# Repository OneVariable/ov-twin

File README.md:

# OneVariable Twin Trainer Hardware

Hardware for the OV Twin Trainer Board.

Designed for [RustNL 2024 Workshops](https://2024.rustnl.org/workshops/)

## Schematic

You can view the PDF schematic [here](./assets/ov-twin.pdf).

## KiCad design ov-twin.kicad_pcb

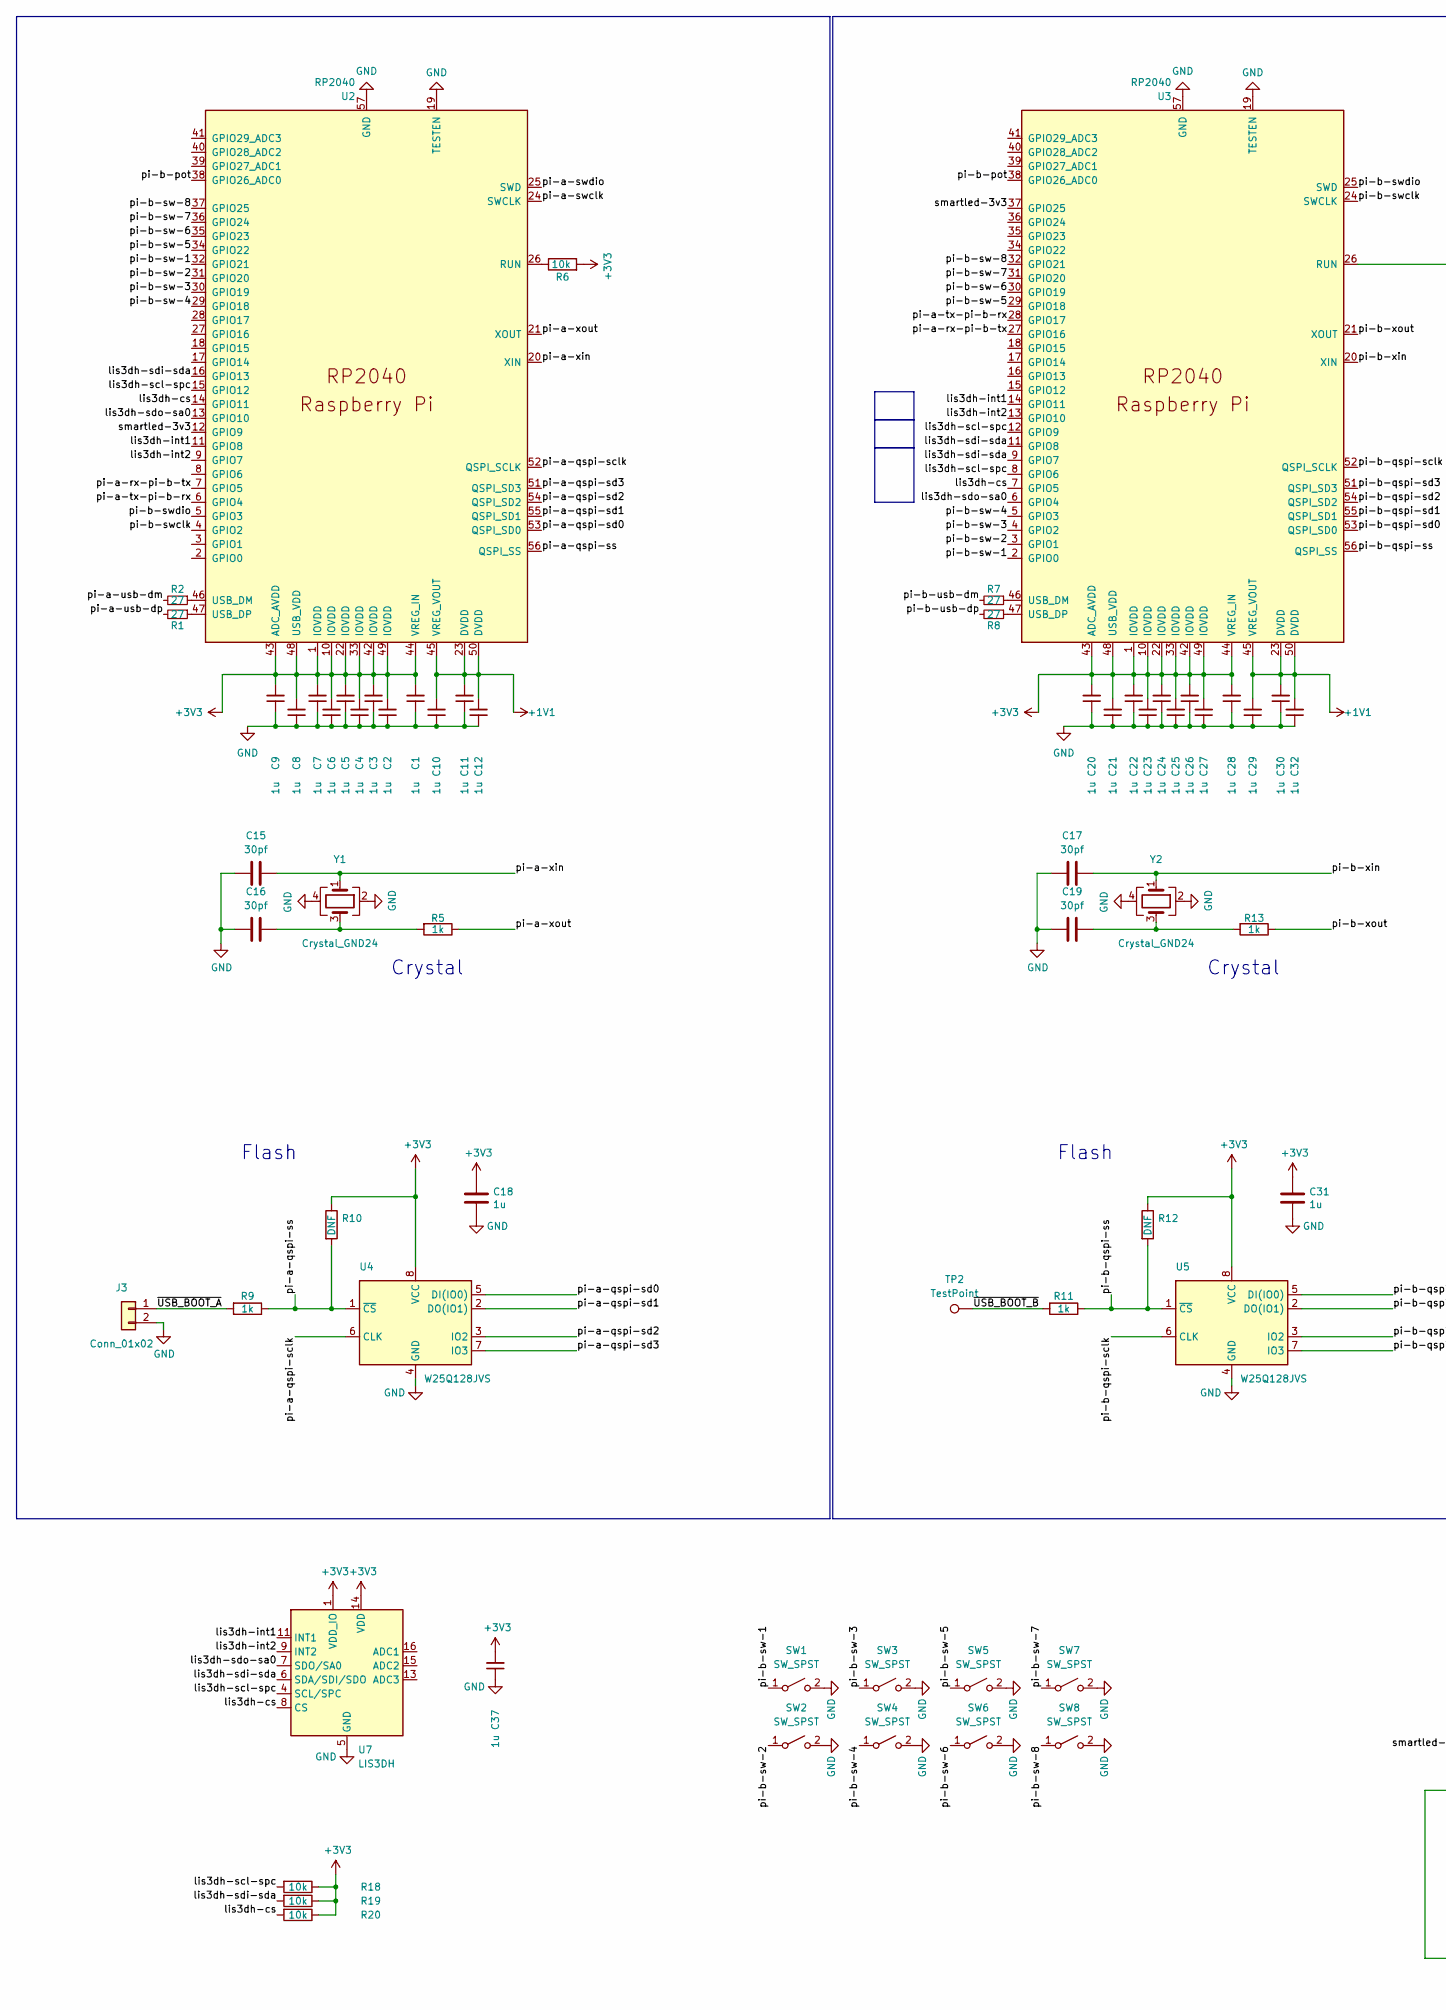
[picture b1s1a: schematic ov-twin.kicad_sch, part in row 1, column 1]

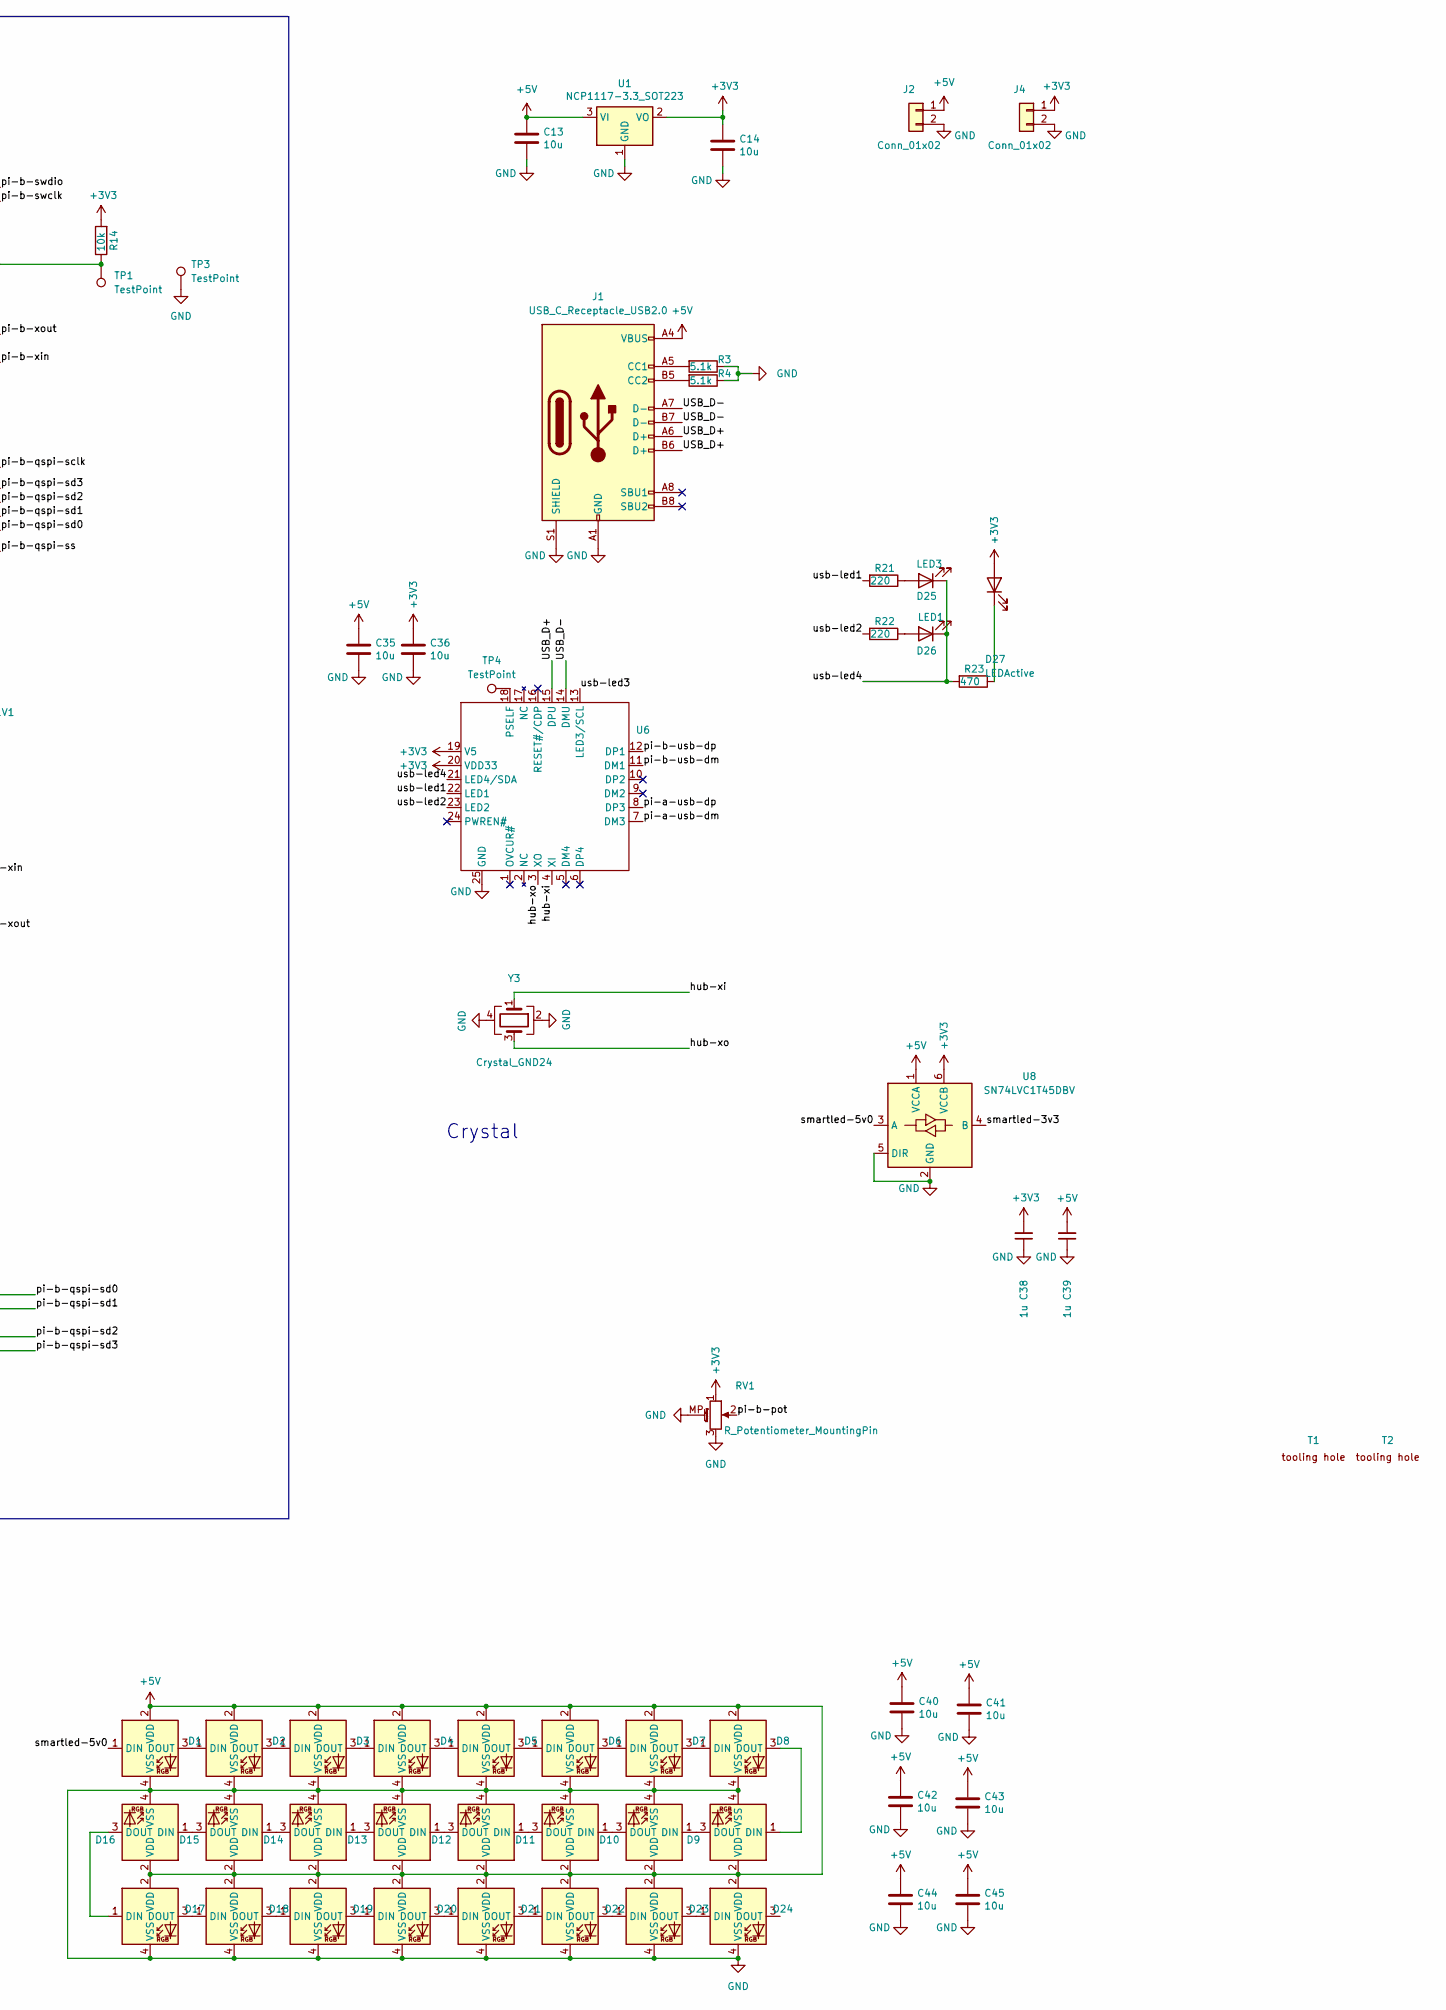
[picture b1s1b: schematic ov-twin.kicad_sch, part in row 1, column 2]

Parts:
C1, C2, C3, C4, C5, C6, C7, C8, C9, C10, C11, C12, C20, C21, C22, C23, C24, C25, C26, C27, C28, C29, C30, C32, C37, C38, C39: 1u; C_0402_1005Metric
C13, C14, C35, C36, C40, C41, C42, C43, C44, C45: 10u; C_0805_2012Metric
C15, C16, C17, C19: 30pf; C_0603_1608Metric
C18, C31: 1u; C_0805_2012Metric
D1, D2, D3, D4, D5, D6, D7, D8, D9, D10, D11, D12, D13, D14, D15, D16, D17, D18, D19, D20, D21, D22, D23, D24: LED_WS2812B-2020_PLCC4_2.0x2.0mm
D25: LED3; LED_0603_1608Metric
D26: LED1; LED_0603_1608Metric
D27: LEDActive; LED_0603_1608Metric
J1: USB_C_Receptacle_USB2.0; USB_C_Receptacle_G-Switch_GT-USB-7010ASV
J2, J3, J4: Conn_01x02; PinHeader_1x02_P2.54mm_Vertical
R1, R2, R7, R8: 27; R_0402_1005Metric
R3, R4: 5.1k; R_0402_1005Metric
R5, R9, R11, R13: 1k; R_0402_1005Metric
R6, R14, R18, R19, R20: 10k; R_0402_1005Metric
R10, R12: DNF; R_0402_1005Metric
R21, R22: 220; R_0402_1005Metric
R23: 470; R_0402_1005Metric
RV1: R_Potentiometer_MountingPin; Potentiometer_Alps_RK09K_Single_Vertical
SW1, SW2, SW3, SW4, SW5, SW6, SW7, SW8: SW_SPST; k2-1817UQ
T1, T2: tooling-hole
TP1, TP2, TP3, TP4: TestPoint; TestPoint_Pad_D1.5mm
U1: NCP1117-3.3_SOT223; SOT-223-3_TabPin2
U2, U3: RP2040; RP2040-QFN-56
U4, U5: W25Q128JVS; SOIC-8_5.23x5.23mm_P1.27mm
U6: QFN-24-1EP_4x4mm_P0.5mm_EP2.7x2.7mm_ThermalVias
U7: LIS3DH; LGA-16_3x3mm_P0.5mm_LayoutBorder3x5y
U8: SN74LVC1T45DBV; SOT-23-6
Y1, Y2, Y3: Crystal_GND24; Crystal_SMD_3225-4Pin_3.2x2.5mm

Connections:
+1V1: C10.2, C11.2, C12.2, C29.2, C30.2, C32.2, U2.23 (DVDD), U2.45 (VREG_VOUT), U2.50 (DVDD), U3.23 (DVDD), U3.45 (VREG_VOUT), U3.50 (DVDD)
+3V3: C1.2, C2.2, C3.2, C4.2, C5.2, C6.2, C7.2, C8.2, C9.2, C14.1, C18.1, C20.2, C21.2, C22.2, C23.2, C24.2, C25.2, C26.2, C27.2, C28.2, C31.1, C36.1, C37.2, C38.2, D27.2 (A), J4.1, R6.2, R10.1, R12.1, R14.2, R18.1, R19.1, R20.1, RV1.1, U1.2 (VO), U2.1 (IOVDD), U2.10 (IOVDD), U2.22 (IOVDD), U2.33 (IOVDD), U2.42 (IOVDD), U2.43 (ADC_AVDD), U2.44 (VREG_IN), U2.48 (USB_VDD), U2.49 (IOVDD), U3.1 (IOVDD), U3.10 (IOVDD), U3.22 (IOVDD), U3.33 (IOVDD), U3.42 (IOVDD), U3.43 (ADC_AVDD), U3.44 (VREG_IN), U3.48 (USB_VDD), U3.49 (IOVDD), U4.8 (VCC), U5.8 (VCC), U6.19 (V5), U6.20 (VDD33), U7.1 (VDD_IO), U7.14 (VDD), U8.6 (VCCB)
+5V: C13.1, C35.1, C39.2, C40.1, C41.1, C42.1, C43.1, C44.1, C45.1, D1.2 (VDD), D2.2 (VDD), D3.2 (VDD), D4.2 (VDD), D5.2 (VDD), D6.2 (VDD), D7.2 (VDD), D8.2 (VDD), D9.2 (VDD), D10.2 (VDD), D11.2 (VDD), D12.2 (VDD), D13.2 (VDD), D14.2 (VDD), D15.2 (VDD), D16.2 (VDD), D17.2 (VDD), D18.2 (VDD), D19.2 (VDD), D20.2 (VDD), D21.2 (VDD), D22.2 (VDD), D23.2 (VDD), D24.2 (VDD), J1.A4 (VBUS), J1.A9 (VBUS), J1.B4 (VBUS), J1.B9 (VBUS), J2.1, U1.3 (VI), U8.1 (VCCA)
/USB_D+: J1.A6 (D+), J1.B6 (D+), U6.15 (DPU)
/USB_D-: J1.A7 (D-), J1.B7 (D-), U6.14 (DMU)
/hub-xi: U6.4 (XI), Y3.1
/hub-xo: U6.3 (XO), Y3.3
/lis3dh-cs: R20.2, U2.14 (GPIO11), U3.7 (GPIO5), U7.8 (CS)
/lis3dh-int1: U2.11 (GPIO8), U3.14 (GPIO11), U7.11 (INT1)
/lis3dh-int2: U2.9 (GPIO7), U3.13 (GPIO10), U7.9 (INT2)
/lis3dh-scl-spc: R18.2, U2.15 (GPIO12), U3.8 (GPIO6), U3.12 (GPIO9), U7.4 (SCL/SPC)
/lis3dh-sdi-sda: R19.2, U2.16 (GPIO13), U3.9 (GPIO7), U3.11 (GPIO8), U7.6 (SDA/SDI/SDO)
/lis3dh-sdo-sa0: U2.13 (GPIO10), U3.6 (GPIO4), U7.7 (SDO/SA0)
/pi-a-qspi-sclk: U2.52 (QSPI_SCLK), U4.6 (CLK)
/pi-a-qspi-sd0: U2.53 (QSPI_SD0), U4.5 (DI(IO0))
/pi-a-qspi-sd1: U2.55 (QSPI_SD1), U4.2 (DO(IO1))
/pi-a-qspi-sd2: U2.54 (QSPI_SD2), U4.3 (IO2)
/pi-a-qspi-sd3: U2.51 (QSPI_SD3), U4.7 (IO3)
/pi-a-qspi-ss: R9.1, R10.2, U2.56 (QSPI_SS), U4.1 (~CS)
/pi-a-rx-pi-b-tx: U2.7 (GPIO5), U3.27 (GPIO16)
/pi-a-swclk: U2.24 (SWCLK)
/pi-a-swdio: U2.25 (SWD)
/pi-a-tx-pi-b-rx: U2.6 (GPIO4), U3.28 (GPIO17)
/pi-a-usb-dm: R2.2, U6.7 (DM3)
/pi-a-usb-dp: R1.2, U6.8 (DP3)
/pi-a-xin: C15.2, U2.20 (XIN), Y1.1
/pi-a-xout: R5.1, U2.21 (XOUT)
/pi-b-pot: RV1.2, U2.38 (GPIO26_ADC0), U3.38 (GPIO26_ADC0)
/pi-b-qspi-sclk: U3.52 (QSPI_SCLK), U5.6 (CLK)
/pi-b-qspi-sd0: U3.53 (QSPI_SD0), U5.5 (DI(IO0))
/pi-b-qspi-sd1: U3.55 (QSPI_SD1), U5.2 (DO(IO1))
/pi-b-qspi-sd2: U3.54 (QSPI_SD2), U5.3 (IO2)
/pi-b-qspi-sd3: U3.51 (QSPI_SD3), U5.7 (IO3)
/pi-b-qspi-ss: R11.1, R12.2, U3.56 (QSPI_SS), U5.1 (~CS)
/pi-b-sw-1: SW1.1 (A), U2.32 (GPIO21), U3.2 (GPIO0)
/pi-b-sw-2: SW2.1 (A), U2.31 (GPIO20), U3.3 (GPIO1)
/pi-b-sw-3: SW3.1 (A), U2.30 (GPIO19), U3.4 (GPIO2)
/pi-b-sw-4: SW4.1 (A), U2.29 (GPIO18), U3.5 (GPIO3)
/pi-b-sw-5: SW5.1 (A), U2.34 (GPIO22), U3.29 (GPIO18)
/pi-b-sw-6: SW6.1 (A), U2.35 (GPIO23), U3.30 (GPIO19)
/pi-b-sw-7: SW7.1 (A), U2.36 (GPIO24), U3.31 (GPIO20)
/pi-b-sw-8: SW8.1 (A), U2.37 (GPIO25), U3.32 (GPIO21)
/pi-b-swclk: U2.4 (GPIO2), U3.24 (SWCLK)
/pi-b-swdio: U2.5 (GPIO3), U3.25 (SWD)
/pi-b-usb-dm: R7.2, U6.11 (DM1)
/pi-b-usb-dp: R8.2, U6.12 (DP1)
/pi-b-xin: C17.2, U3.20 (XIN), Y2.1
/pi-b-xout: R13.1, U3.21 (XOUT)
/smartled-3v3: U2.12 (GPIO9), U3.37 (GPIO25), U8.4 (B)
/smartled-5v0: D1.1 (DIN), U8.3 (A)
/usb-led1: R21.2, U6.22 (LED1)
/usb-led2: R22.2, U6.23 (LED2)
/usb-led3: U6.13 (LED3/SCL)
/usb-led4: D25.1 (K), D26.1 (K), R23.2, U6.21 (LED4/SDA)
/~USB_BOOT_A: J3.1, R9.2
/~USB_BOOT_B: R11.2, TP2.1
GND: C1.1, C2.1, C3.1, C4.1, C5.1, C6.1, C7.1, C8.1, C9.1, C10.1, C11.1, C12.1, C13.2, C14.2, C15.1, C16.1, C17.1, C18.2, C19.1, C20.1, C21.1, C22.1, C23.1, C24.1, C25.1, C26.1, C27.1, C28.1, C29.1, C30.1, C31.2, C32.1, C35.2, C36.2, C37.1, C38.1, C39.1, C40.2, C41.2, C42.2, C43.2, C44.2, C45.2, D1.4 (VSS), D2.4 (VSS), D3.4 (VSS), D4.4 (VSS), D5.4 (VSS), D6.4 (VSS), D7.4 (VSS), D8.4 (VSS), D9.4 (VSS), D10.4 (VSS), D11.4 (VSS), D12.4 (VSS), D13.4 (VSS), D14.4 (VSS), D15.4 (VSS), D16.4 (VSS), D17.4 (VSS), D18.4 (VSS), D19.4 (VSS), D20.4 (VSS), D21.4 (VSS), D22.4 (VSS), D23.4 (VSS), D24.4 (VSS), J1.A1 (GND), J1.A12 (GND), J1.B1 (GND), J1.B12 (GND), J1.S1 (SHIELD), J2.2, J3.2, J4.2, R3.1, R4.1, RV1.3, RV1.MP (MountPin), SW1.2 (B), SW2.2 (B), SW3.2 (B), SW4.2 (B), SW5.2 (B), SW6.2 (B), SW7.2 (B), SW8.2 (B), TP3.1, U1.1 (GND), U2.19 (TESTEN), U2.57 (GND), U3.19 (TESTEN), U3.57 (GND), U4.4 (GND), U5.4 (GND), U6.25 (GND), U7.5 (GND), U7.10 (GND), U7.12 (GND), U8.2 (GND), U8.5 (DIR), Y1.2, Y1.4, Y2.2, Y2.4, Y3.2, Y3.4
unnamed: C16.2, R5.2, Y1.3
unnamed: C19.2, R13.2, Y2.3
unnamed: D1.3 (DOUT), D2.1 (DIN)
unnamed: D2.3 (DOUT), D3.1 (DIN)
unnamed: D3.3 (DOUT), D4.1 (DIN)
unnamed: D4.3 (DOUT), D5.1 (DIN)
unnamed: D5.3 (DOUT), D6.1 (DIN)
unnamed: D6.3 (DOUT), D7.1 (DIN)
unnamed: D7.3 (DOUT), D8.1 (DIN)
unnamed: D8.3 (DOUT), D9.1 (DIN)
unnamed: D9.3 (DOUT), D10.1 (DIN)
unnamed: D10.3 (DOUT), D11.1 (DIN)
unnamed: D11.3 (DOUT), D12.1 (DIN)
unnamed: D12.3 (DOUT), D13.1 (DIN)
unnamed: D13.3 (DOUT), D14.1 (DIN)
unnamed: D14.3 (DOUT), D15.1 (DIN)
unnamed: D15.3 (DOUT), D16.1 (DIN)
unnamed: D16.3 (DOUT), D17.1 (DIN)
unnamed: D17.3 (DOUT), D18.1 (DIN)
unnamed: D18.3 (DOUT), D19.1 (DIN)
unnamed: D19.3 (DOUT), D20.1 (DIN)
unnamed: D20.3 (DOUT), D21.1 (DIN)
unnamed: D21.3 (DOUT), D22.1 (DIN)
unnamed: D22.3 (DOUT), D23.1 (DIN)
unnamed: D23.3 (DOUT), D24.1 (DIN)
unnamed: D25.2 (A), R21.1
unnamed: D26.2 (A), R22.1
unnamed: D27.1 (K), R23.1
unnamed: J1.A5 (CC1), R3.2
unnamed: J1.B5 (CC2), R4.2
unnamed: R6.1, U2.26 (RUN)
unnamed: R2.1, U2.46 (USB_DM)
unnamed: R1.1, U2.47 (USB_DP)
unnamed: R14.1, TP1.1, U3.26 (RUN)
unnamed: R7.1, U3.46 (USB_DM)
unnamed: R8.1, U3.47 (USB_DP)
unnamed: TP4.1, U6.18 (PSELF)

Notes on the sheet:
Crystal
Flash

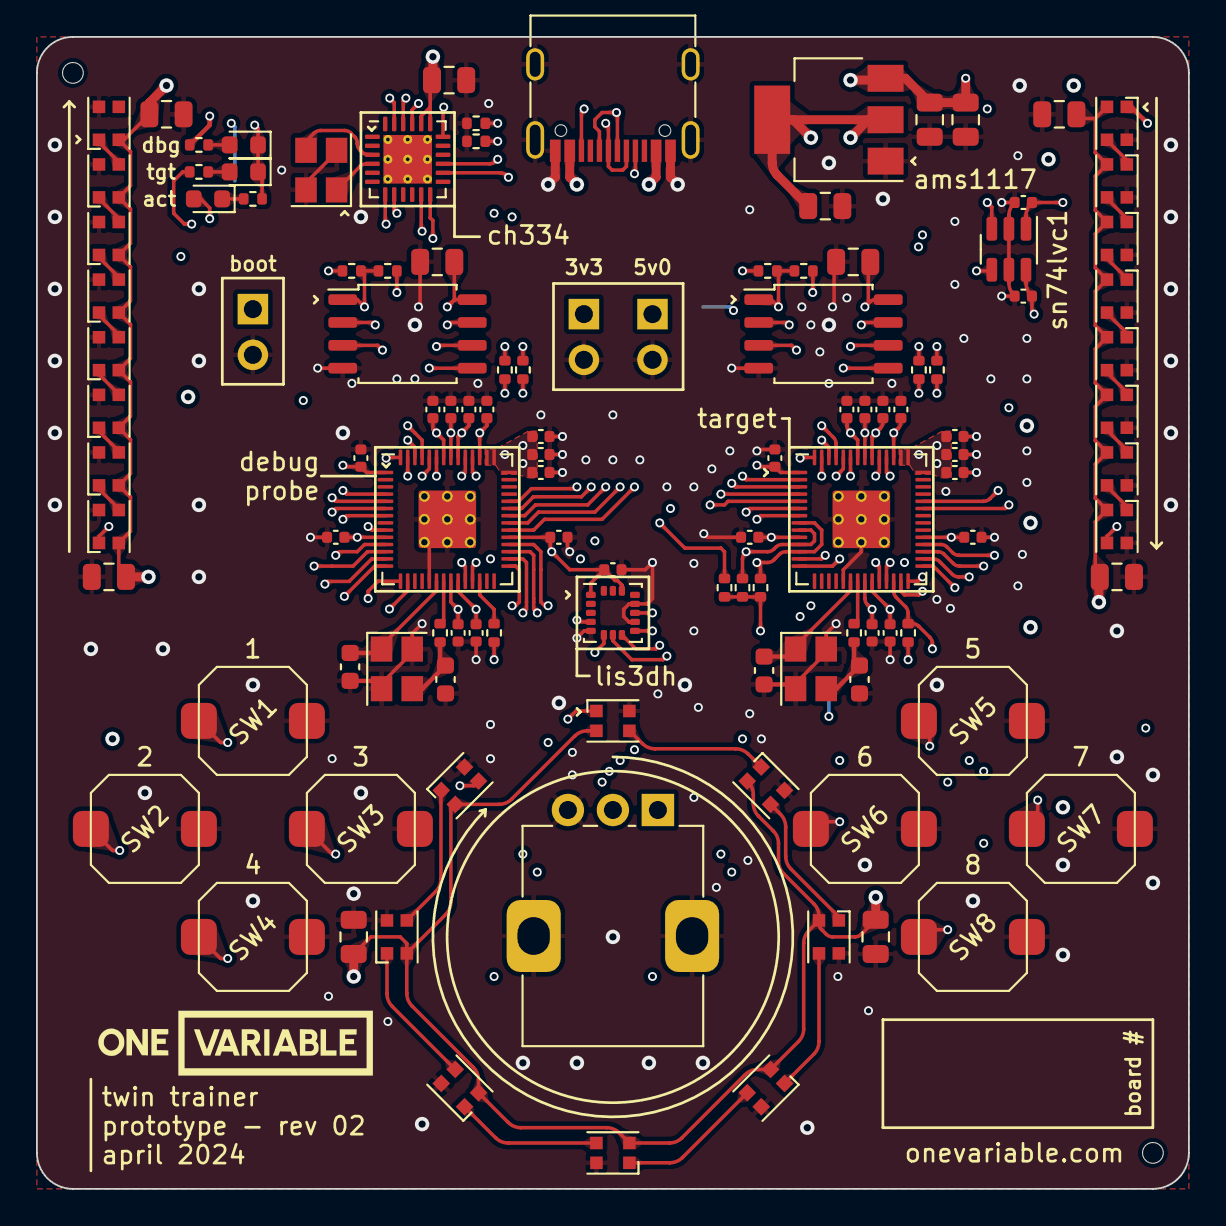
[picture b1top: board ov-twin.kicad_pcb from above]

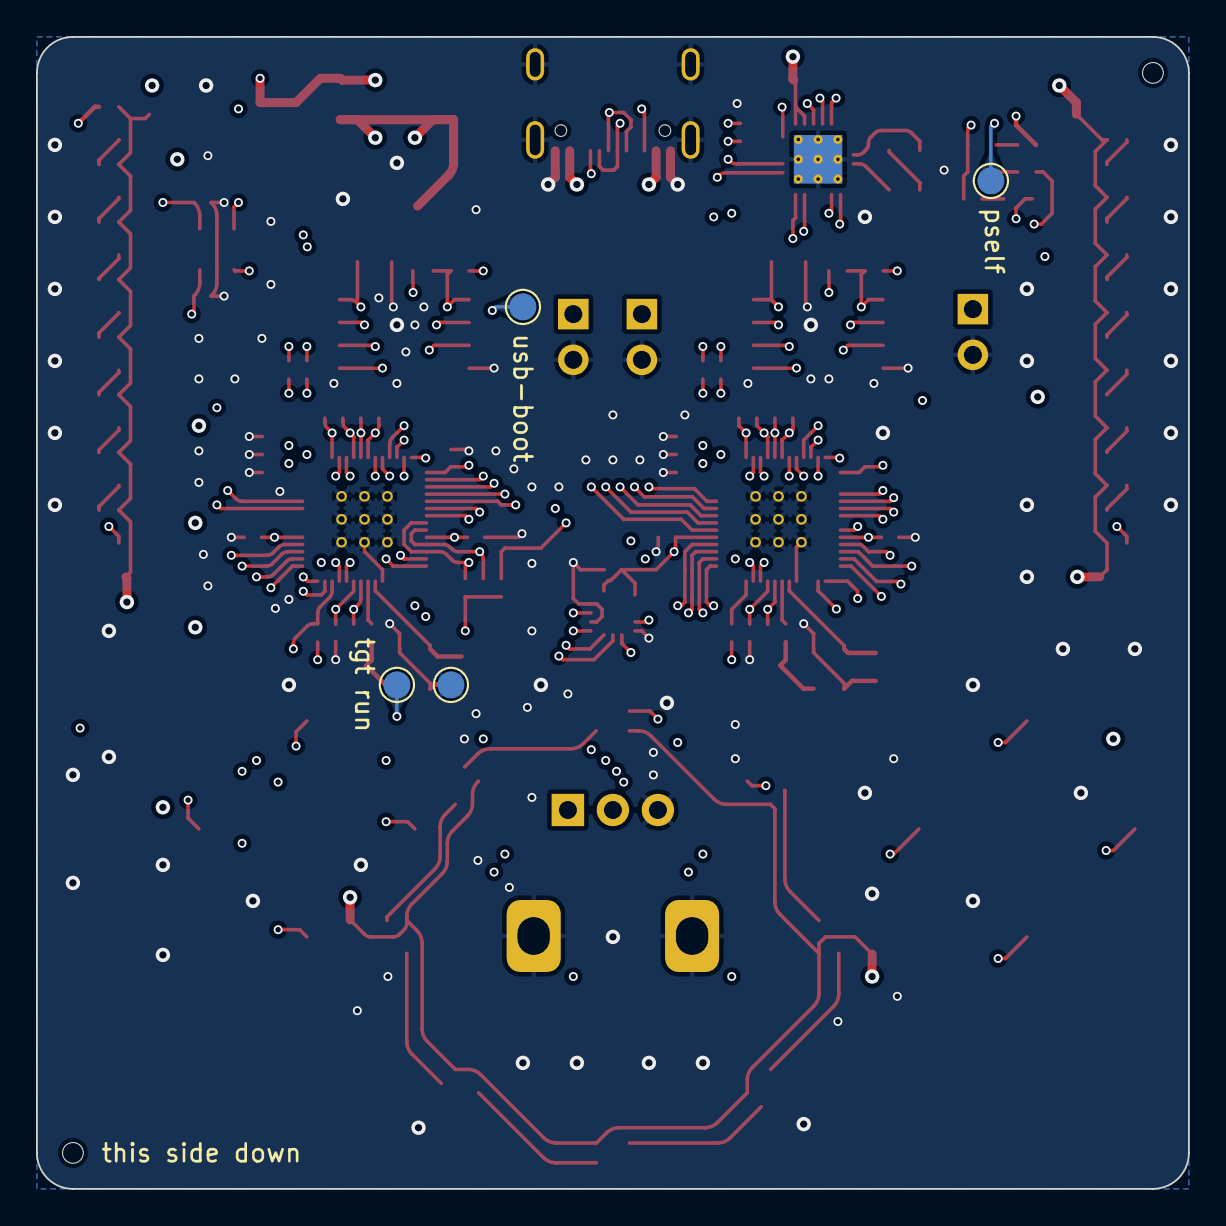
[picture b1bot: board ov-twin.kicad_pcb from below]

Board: 4 copper layers, 64.0 x 64.0 mm, 120 parts (4 on the bottom side), 91 nets.

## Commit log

2024-03-13 One rp2040 placed and mostly routed
2024-03-14 Hub and stuff
2024-03-15 Mostly routed, wondering how to do sniffing
2024-03-15 Okay let's try it
2024-03-15 Add missing decoupling and such
2024-03-15 That worked pretty well I thought!
2024-04-11 Second order
2024-04-11 Add readme
2024-05-03 Plot schematic (and clean up schematic a bit)
2024-05-03 Add link to schematic
